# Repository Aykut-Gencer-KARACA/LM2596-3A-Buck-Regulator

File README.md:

<div align="center">

<br/>

<br/><br/>

**Giriş gerilimini düşürüp çıkışa aktaran, trimpotla ayarlanabilir 3 A buck regülatör kartı.**<br/>
LM2596-ADJ ile kurulu bir SMPS (anahtarlamalı güç kaynağı) devresi; üç revizyonda küçültülerek üretime hazır hale getirildi.

</div>

## İçindekiler

- [Genel bakış](#-genel-bakış)
- [Öne çıkanlar](#-öne-çıkanlar)
- [Sistem mimarisi](#-sistem-mimarisi)
- [Çalışma prensibi](#-çalışma-prensibi)
- [Donanım](#-donanım)
- [Tasarım hesapları](#-tasarım-hesapları)
- [Simülasyon](#-simülasyon)
- [Şematik](#-şematik)
- [PCB](#-pcb)
- [Revizyonlar](#-revizyonlar)
- [Malzeme listesi](#-malzeme-listesi)
- [Depo yapısı](#-depo-yapısı)

## ◆ Genel bakış

Bu projede giriş gerilimi düşürülerek çıkışa aktarılır. Giriş gerilimini düşüren bu tip devrelere **SMPS** (Switched-Mode Power Supply) denir; bu projede **LM2596S-ADJ** kullanılmıştır. Çıkış gerilimi, geri besleme bölücüsündeki **RV1** trimpotuyla ayarlanır.

| Özellik | Değer |
|---|---|
| **Regülatör** | LM2596S-ADJ · TO-263-5 · 150 kHz anahtarlama (datasheet) |
| **Çıkış akımı** | 3 A |
| **Giriş gerilimi** | LM2596 için 4.5 – 40 V (datasheet); kondansatörler 50 V |
| **Çıkış gerilimi** | 1.23 V (RV1 = 0) – 13.5 V (RV1 = 10 kΩ), $V_{OUT} = 1.23 \times (1 + R_{V1}/R_1)$ |
| **Bobin** | L1 47 µH · doyma akımı 4.5 A |
| **Serbest dolaşım diyodu** | D1 SS36 · 3 A · 60 V Schottky |
| **Kondansatörler** | C1, C4 470 µF 50 V · C2, C3 100 nF 50 V |
| **Bağlantı** | Giriş ve çıkış için köşelerde 2.2 mm delikli 4 adet pad (IN+, IN−, OUT+, OUT−) · şematikte J1 / J2 olarak çizilen 3.5 mm vida klemens (DB301V-3.5-2P, LCSC C695629) için PCB'de footprint yoktur |
| **Kart (RevC)** | 46.63 × 24.10 mm · 2 katmanlı · 1.6 mm |
| **Maliyet (RevC)** | ≈ 1.05 USD / kart (100 adet) · ≈ 0.83 USD / kart (1000 adet) |

## ◆ Öne çıkanlar

<table>
<tr>
<td width="50%" valign="top">

**Üç revizyonda küçülen kart**<br/>
RevA 56.85 × 32.82 mm, RevB 60.26 × 24.56 mm, RevC 46.63 × 24.10 mm. RevC, RevA'ya göre kart alanını yaklaşık %40 azaltır (1865 mm² → 1124 mm²).

</td>
<td width="50%" valign="top">

**Üretime hazır**<br/>
Güncel sürüm RevC'nin KiCad projesi depoda; LCSC stok kodlu parça listesi ve maliyet tablosu aşağıdaki Malzeme listesi bölümündedir.

</td>
</tr>
<tr>
<td valign="top">

**Ayarlanabilir çıkış**<br/>
Geri besleme direnci 1 kΩ (R1) ile 10 kΩ'luk çok turlu trimpot (RV1) birlikte çıkış gerilimini belirler; ince ayar için 3296W tipi çok turlu trimpot seçildi.

</td>
<td valign="top">

**Seçilmiş pasif parçalar**<br/>
Girişte ve çıkışta 470 µF / 50 V kondansatörler ani akım ihtiyacını karşılar; 100 nF seramikler yüksek frekanslı gürültüyü bastırır.

</td>
</tr>
</table>

## ◆ Sistem mimarisi

Güç yolu soldan sağa akıyor: giriş (J1) önce C1 / C2 filtresinden geçip LM2596'nın `VIN` pinine ulaşıyor. LM2596'nın içindeki anahtar, `OUT` (SW) düğümünü yüksek frekansta giriş gerilimine bağlayıp ayırıyor. Anahtar açıldığında D1, bobin akımını serbest dolaşım yoluyla yüke taşıyor. L1 ve C3 / C4 bir LC süzgeç oluşturup çıkış gerilimini düzeltiyor. Çıkış gerilimi R1 ve RV1 ile bölünüp `FB` pinine geri besleniyor; LM2596 bu pini 1.23 V'ta tutacak şekilde duty'yi ayarlıyor.

## ◆ Çalışma prensibi

Anahtar iletimdeyken (**ON**) akım `V_IN → S → L1 → yük` yolunu izler ve bobin akımı artar. Anahtar açıldığında (**OFF**) bobin akımını sürdürmek ister; D1 iletime geçer ve akım `D1 → L1 → yük` yolunda dolaşarak azalır. Duty oranı çıkış gerilimini belirler:

$$V_{OUT} = D \times V_{IN}$$

## ◆ Donanım

<details open>
<summary><b>Güç katı</b></summary>
<br/>

| Blok | Parça | Not |
|---|---|---|
| Regülatör | U1 LM2596S-ADJ | TO-263-5, 3 A, iç anahtar |
| Bobin | L1 SMMS1040-470M · 47 µH | ISAT 4.5 A · Irms 3 A · DCR 155 mΩ · SMD 11.5 × 10.0 mm (LCSC C149599) |
| Diyot | D1 SS36 · 3 A · 60 V Schottky | DO-214AC (SMA) |
| Giriş kondansatörleri | C1 470 µF 50 V (THT) · C2 100 nF 50 V (0402) | Çıkıştaki ani akım ihtiyacını karşılar ve gerilim çakılmasını önler |
| Çıkış kondansatörleri | C4 470 µF 50 V (THT) · C3 100 nF 50 V (0402) | Çıkıştaki dalgalanmayı (ripple) düşürür |
| Bağlantılar | IN+, IN−, OUT+, OUT− pad'leri | 2.2 mm delikli (3.8 mm pad) lehim noktaları; şematikteki J1 / J2 klemensi PCB'ye yerleştirilmemiştir |

</details>

<details>
<summary><b>Geri besleme</b></summary>
<br/>

- **R1** (1 kΩ, 0805) FB pininden GND'ye bağlıdır.
- **RV1** (10 kΩ, 3296W) çıkış ile FB pini arasında reosta olarak bağlıdır (3 numaralı uç çıkışta, kayar kontak FB'de; 1 numaralı uç boştadır).
- `ON/OFF` pini GND'ye bağlıdır; regülatör her zaman açıktır.

</details>

## ◆ Tasarım hesapları

> Değerler KiCad şematik / PCB dosyalarından (RevC) ve TI LM2596 datasheet'inden (SNVS124G) alınmıştır; her kural için datasheet bölümü belirtilmiştir. Datasheet'te karşılığı olmayan değerler "varsayım" diye işaretlenmiştir.

<details>
<summary><b>Çıkış gerilimi ve geri besleme</b></summary>
<br/>

LM2596 FB pinini $V_{REF} = 1.23\text{ V}$'ta tutar (datasheet 7.8: 1.193 – 1.267 V). R1 FB–GND, RV1 OUT–FB arasında olduğu için (Denklem 5):

$$V_{OUT} = V_{REF} \times \left(1 + \frac{R_{V1}}{R_1}\right) = 1.23\text{ V} \times \left(1 + \frac{R_{V1}}{1\text{ k}\Omega}\right)$$

R1 = 1 kΩ, datasheet'in önerdiği 240 Ω – 1.5 kΩ aralığındadır (9.2.2.2.1). Bölücüden $I_{FB} = 1.23\text{ V} / 1\text{ k}\Omega = 1.23\text{ mA}$ akar; bu, FB bias akımının (tipik 10 nA) yaklaşık $10^5$ katıdır.

| RV1 | V<sub>OUT</sub> | V<sub>FB</sub> toleransıyla |
|---|---|---|
| 0 Ω | 1.23 V | 1.19 – 1.27 V |
| 1 kΩ | 2.46 V | 2.39 – 2.53 V |
| 2 kΩ | 3.69 V | 3.58 – 3.80 V |
| 4 kΩ | 6.15 V | 5.97 – 6.34 V |
| 7 kΩ | 9.84 V | 9.54 – 10.14 V |
| 10 kΩ | 13.53 V | 13.12 – 13.94 V |

3.3 V için $R_{V1} = 1.68\text{ k}\Omega$, 5 V için 3.07 kΩ, 12 V için 8.76 kΩ gerekir. İç anahtarın doyma gerilimi 3 A'de tipik 1.16 V, en fazla 1.4 V (sıcakta 1.5 V); L1'in DCR değeri 155 mΩ (LCSC C149599) olduğundan bobin üzerinde 3 A'de $3 \times 0.155 = 0.47\text{ V}$ düşer. Giriş gerilimi bu yüzden çıkıştan en az $1.16 + 0.47 = 1.63\text{ V}$ (tipik) – $1.4 + 0.47 = 1.87\text{ V}$ (en kötü) yüksek olmalıdır. 10 V'un üzerindeki çıkışlar için datasheet, RV1'e paralel $C_{FF} = 1/(31 \cdot 10^3 \cdot R_2)$ önerir (12 V'ta ≈ 3.7 nF; Tablo 9-6: 1 nF); kartta bu kondansatör yoktur.

RV1'in 1 numaralı ucu boştadır; kayar kontak geçici olarak açık devre olursa FB pinine çıkıştan akım gelmez ve R1 yüzünden FB 0 V'a iner, regülatör duty'yi artırarak çıkışı giriş gerilimine doğru yükseltir. Datasheet'te bu durum anılmaz; trimpotlarda yaygın uygulama, kullanılmayan ucun kayar kontağa bağlanmasıdır.

</details>

<details>
<summary><b>Çalışma noktaları: duty, bobin dalgalanması, tepe akım</b></summary>
<br/>

Datasheet'in duty ifadesi (Denklem 8; $V_{SAT} = 1.16\text{ V}$, $V_D = 0.5\text{ V}$) ve 150 kHz, $L = 47\ \mu\text{H}$ için dalgalanma:

$$D = \frac{V_{OUT} + V_D}{V_{IN} - V_{SAT} + V_D}, \qquad \Delta I_L = \frac{(V_{IN} - V_{SAT} - V_{OUT})\,D}{f_{sw}\,L}, \qquad I_{pk} = I_{LOAD} + \frac{\Delta I_L}{2}$$

| V<sub>IN</sub> → V<sub>OUT</sub> | D | ΔI<sub>L</sub> (pp) | E·T (V·µs) | I<sub>pk</sub> (3 A) | CCM sınırı ΔI<sub>L</sub>/2 |
|---|---|---|---|---|---|
| 12 V → 3.3 V | 0.335 | 0.36 A | 16.8 | 3.18 A | 0.18 A |
| 12 V → 5 V | 0.485 | 0.40 A | 18.9 | 3.20 A | 0.20 A |
| 24 V → 5 V | 0.236 | 0.60 A | 28.0 | 3.30 A | 0.30 A |
| 24 V → 12 V | 0.536 | 0.82 A | 38.7 | 3.41 A | 0.41 A |
| 36 V → 12 V | 0.354 | 1.15 A | 53.9 | 3.57 A | 0.57 A |
| 40 V → 12 V | 0.318 | 1.21 A | 56.9 | 3.60 A | 0.60 A |

Örnek (24 V → 12 V): $D = 12.5 / 23.34 = 0.536$, $\Delta I_L = 10.84 \times 0.536 / (150\text{ kHz} \times 47\ \mu\text{H}) = 0.82\text{ A}$.

</details>

<details>
<summary><b>Bobin kontrolü</b></summary>
<br/>

Datasheet'in örnek tasarımı (9.2.2.2.2, 28 V → 20 V, 3 A) $E \cdot T = 34.2\text{ V}\cdot\mu\text{s}$ bulup 47 µH seçer; kartın 24 V → 12 V noktası 38.7 V·µs olduğundan 47 µH aynı bölgededir. 12 – 24 V girişte tepe akım ≤ 3.41 A, yani ISAT'ın (4.5 A) %76'sıdır. 40 V → 12 V, 3 A noktasında tepe akım 3.60 A olur ve LM2596'nın en küçük akım sınırına (3.6 A, datasheet 7.9) eşittir; bu bölgede 68 µH bobin tercih edilmelidir.

LCSC kaydına göre L1 (SMMS1040-470M): 47 µH ±%20, Irms 3 A, ISAT 4.5 A, DCR 155 mΩ. 3 A'de bakır kaybı $P_L = I^2 \times DCR = 3^2 \times 0.155 = 1.40\text{ W}$'tır ve nominal akım (3 A) ile yük akımı eşittir; yani bobin tam yükte kendi sıcaklık artış sınırında çalışır.

</details>

<details>
<summary><b>Serbest dolaşım diyodu (D1)</b></summary>
<br/>

| Kural (datasheet 9.2.2.2.5) | Gerekli | SS36 | Sonuç |
|---|---|---|---|
| Ters gerilim ≥ 1.25 × V<sub>IN,max</sub> | 1.25 × 40 V = 50 V | 60 V | sağlanıyor |
| Akım ≥ 1.3 × I<sub>LOAD</sub> | 1.3 × 3 A = 3.9 A | 3 A | sağlanmıyor |
| Sürekli kısa devre: akım ≥ I<sub>CL</sub> | 4.5 A (tipik) | 3 A | sağlanmıyor |

Normal çalışmada ortalama diyot akımı $I_D = I_{LOAD}(1 - D)$ ve kaybı $P_D = 0.5\text{ V} \times I_D$: 12 V → 5 V için 1.54 A / 0.77 W, 24 V → 12 V için 1.39 A / 0.70 W, 24 V → 5 V için 2.29 A / 1.15 W. Normal yükte 3 A'lik diyot yeterlidir; kalıcı kısa devre dayanımı için 5 A sınıfı gerekir.

</details>

<details>
<summary><b>Kondansatörler</b></summary>
<br/>

- **C1 (giriş):** RMS akım değeri $\ge I_{LOAD}/2 = 1.5\text{ A}$ ve gerilim değeri $\approx 1.5 \times V_{IN}$ olmalıdır (9.2.2.2.6); 50 V için bu $V_{IN} \le 33\text{ V}$ demektir. RMS değeri üretici datasheet'inden doğrulanmalıdır (şematikte parça numarası yoktur, BOM'daki 01EC4236 kodu doğrulanamadı).
- **C4 (çıkış):** datasheet 82 – 820 µF aralığını ve $\ge 1.5 \times V_{OUT}$ gerilim değerini ister (9.2.2.2.3); 470 µF / 50 V bunu sağlar (13.5 V için gereken 20.3 V).
- **Çıkış dalgalanması:** $V_{rip} = \Delta I_L \cdot ESR$; 24 V → 12 V noktasında kapasitif bileşen $\Delta I_L / (8 f_{sw} C) = 1.5\text{ mV}$ (ihmal edilebilir). ESR bileşeni (ESR varsayım): 0.05 Ω için 41 mV, 0.1 Ω için 82 mV, 0.2 Ω için 165 mV (pp).

$$f_0 = \frac{1}{2\pi\sqrt{L_1 C_4}} = \frac{1}{2\pi\sqrt{47\ \mu\text{H} \times 470\ \mu\text{F}}} \approx 1.07\text{ kHz} \quad\Rightarrow\quad \frac{150\text{ kHz}}{1.07\text{ kHz}} \approx 140$$

</details>

<details>
<summary><b>Güç kaybı ve ısıl kontrol</b></summary>
<br/>

İç anahtarın iletim ve besleme kaybı (alt sınır): $P_{IC,min} = V_{SAT}\,I_{LOAD}\,D + V_{IN}\,I_Q$ ($I_Q = 5\text{ mA}$). Üst sınır, datasheet'in tipik verimlerinden (12 V → 5 V için %80, 25 V → 12 V için %90, 3 A) toplam kayıptan diyot kaybının düşülmesiyle bulunur:

| V<sub>IN</sub> → V<sub>OUT</sub>, 3 A | P<sub>OUT</sub> | η | P<sub>kayıp</sub> | P<sub>D1</sub> | P<sub>L1</sub> (1.40 W) çıkarılınca P<sub>IC</sub> | İletim modeli P<sub>IC</sub> |
|---|---|---|---|---|---|---|
| 12 V → 5 V | 15 W | %80 | 3.75 W | 0.77 W | 1.58 W | 1.75 W |
| 24 V → 12 V | 36 W | %90 | 4.00 W | 0.70 W | 1.90 W | 1.98 W |

İki yöntem birbirine yakındır (1.6 – 2.0 W); yani entegrenin gücü yaklaşık 2 W kabul edilebilir. TO-263 için R<sub>θJA</sub> bakır alanına bağlıdır (datasheet 7.4): 0.5 in² → 50 °C/W, 2.5 in² → 30 °C/W, çift yüzlü 3 in² → 20 °C/W. Kartın tüm alanı $46.63 \times 24.10 = 1124\text{ mm}^2 \approx 1.74\text{ in}^2$ olduğundan 30 – 50 °C/W beklenir. 125 °C sınırı ve 40 °C ortam için izin verilen güç ve 24 V → 12 V, 3 A noktasındaki sıcaklık:

$$P_{IC,max} = \frac{125 - 40}{R_{\theta JA}} = 1.70\text{ W}\ (50\ ^\circ\text{C/W}),\quad 2.83\text{ W}\ (30\ ^\circ\text{C/W}) \qquad T_J = 40 + 1.98 \times R_{\theta JA} = 99\ ^\circ\text{C}\ (30),\quad 139\ ^\circ\text{C}\ (50)$$

R<sub>θJA</sub> = 30 °C/W kadar bakır sağlanıyorsa 3 A tam yük sınırın içindedir; 50 °C/W'ta (az bakır) 125 °C aşılır. Sürekli yük yaklaşık 2 A tutulursa entegre gücü yaklaşık 1.4 W'a (T<sub>J</sub> ≤ 110 °C) düşer. Datasheet 2 A üstünde çift yüzlü kart, geniş bakır alan veya hava akışı önerir (9.4.3); bu nedenle gerçek sıcaklık ölçülmelidir. 24 V → 12 V, 3 A noktasında giriş akımı $36 / (0.9 \times 24) = 1.67\text{ A}$'dir.

</details>

<details>
<summary><b>Seçim gerekçeleri</b></summary>
<br/>

- **Bobin:** RevA'da 68 µH kullanıldı; RevB / RevC'de stok durumu ve maliyet nedeniyle 47 µH (SMMS1040) kullanıldı.
- **Diyot:** Devreden geçecek akım 3 A düzeyinde olacağından serbest dolaşım diyodu Schottky olarak seçildi. RevA'da 5 A'lik bir diyot düşünülmüştü, RevB / RevC'de maliyet için 3 A / 60 V SS36'ya geçildi.
- **Kondansatörler:** Girişte ve çıkışta 50 V dayanımlı 470 µF polarize kondansatörler kullanıldı; RevA'da çıkışta 35 V'luk 220 µF kondansatörler vardı.

</details>

## ◆ Simülasyon

LTspice simülasyon sonucu (Temmuz 2026, tasarımın ilk aşamasında alınmıştır):

## ◆ Şematik

## ◆ PCB

<table>
<tr>
<td width="50%"></td>
<td width="50%"></td>
</tr>
<tr>
<td align="center"><sub>Hero görünüm (sol önden, 3/4) · RevC</sub></td>
<td align="center"><sub>Üstten görünüm · 46.63 × 24.10 mm</sub></td>
</tr>
</table>

Görseller [DRC Analyzer](https://github.com/Aykut-Gencer-KARACA/DRC-Analyzer) ile projenin 3B modelinden üretilmiştir; tam çözünürlüklü dosyalar `KiCad Project/Renders/` klasöründedir.

## ◆ Revizyonlar

**Güncel sürüm: RevC.** Revizyonlar arasında bileşenler stok durumu ve üretim maliyeti nedeniyle değişmiştir.

| | RevA | RevB | RevC |
|---|---|---|---|
| **Kart boyutu** | 56.85 × 32.82 mm | 60.26 × 24.56 mm | 46.63 × 24.10 mm |
| **Bobin (L1)** | 68 µH | 47 µH (SMMS1040) | 47 µH (SMMS1040) |
| **Giriş kondansatörleri** | 2 × 470 µF 50 V | 470 µF 50 V + 100 nF | 470 µF 50 V + 100 nF |
| **Çıkış kondansatörleri** | 2 × 220 µF 35 V | 470 µF 50 V + 100 nF | 470 µF 50 V + 100 nF |
| **Diyot (D1)** | Schottky (genel) | SS36 (3 A, 60 V) | SS36 (3 A, 60 V) |

RevB ve RevC aynı parça listesini kullanır; RevC bu parçaları daha küçük bir kartta toplar.

> [!NOTE]
> RevA'da LM2596 çıkışına paralel bağlı 220 µF kondansatörler ve 5 A'lik Schottky diyot kullanılmıştı. Depoda yalnızca güncel sürüm RevC'nin dosyaları bulunur.

## ◆ Malzeme listesi

<details>
<summary><b>RevC · parça listesi ve maliyet</b> (LCSC stok kodları ve fiyatları)</summary>
<br/>

| Ref | Açıklama | Parça | Adet | Kılıf | Stok kodu |
|---|---|---|:-:|---|---|
| U1 | Buck regülatör | LM2596S-ADJ | 1 | TO-263-5L | LM2596S-ADJ |
| L1 | Güç bobini 47 µH, ISAT 4.5 A, DCR 155 mΩ | SMMS1040-470M | 1 | SMD 11.5 × 10.0 | C149599 |
| D1 | Schottky diyot 3 A / 60 V | SS36 | 1 | DO-214AC | SS36 |
| C1, C4 | 470 µF 50 V | 01EC4236 (doğrulanamadı); footprint'e uyan örnek: Lelon RGA471M1HBK-1020G | 2 | THT D10 × L20, P = 5 mm | 01EC4236 (örnek: C134595) |
| C2, C3 | 100 nF 50 V | C0402B104K500NT | 2 | 0402 | C0402B104K500NT |
| R1 | 1 kΩ, 125 mW | FRC0805F1001TS | 1 | 0805 | FRC0805F1001TS |
| RV1 | 10 kΩ çok turlu trimpot | 3296W-103-LF | 1 | THT 9.5 × 4.8 mm | 3296W-103-LF |
| J1, J2 | Vida klemens, 2 kutuplu, 3.5 mm (7 A, 300 V) · şematikte tanımlı, PCB'de footprint yok | DB301V-3.5-2P-GN-S | 2 | THT | C695629 |

**Maliyet** (parçalar LCSC fiyatlarıyla, kart başına):

| Adet | Toplam | Kart başına | Klemenssiz kart başına |
|---|---|---|---|
| 100 | 104.88 USD | 1.05 USD | 0.93 USD |
| 500 | 438.00 USD | 0.88 USD | 0.78 USD |
| 1000 | 827.90 USD | 0.83 USD | 0.73 USD |

Maliyetler LCSC birim fiyatlarından hesaplanmıştır; fiyatlar ve stok adetleri değişebilir.

</details>

## ◆ Depo yapısı

```text
LM2596-3A-Buck-Regulator/
├─ KiCad Project/                          KiCad projesi (güncel sürüm: RevC)
│  ├─ LM2596-Buck-Regulator.kicad_pro / _sch / _pcb
│  ├─ Layer_Images/                         Katman görüntüleri, şematik PDF, 3D .glb
│  ├─ Renders/                              Yüksek çözünürlüklü PCB render'ı
│  ├─ EasyEDA.kicad_sym                     Sembol kütüphanesi
│  ├─ EasyEDA.pretty/                       Footprint'ler
│  └─ EasyEDA.3dshapes/                     3D modeller
├─ assets/                                 README görselleri
└─ README.md
```

Projeyi açmak için KiCad'de `KiCad Project/LM2596-Buck-Regulator.kicad_pro` dosyasını açın. Revizyon bilgisi şemanın ve PCB'nin başlık bloğundadır.

<br/>

<div align="center">

<br/>
<sub>LM2596 · 47 µH · SS36 · KiCad</sub>
</div>

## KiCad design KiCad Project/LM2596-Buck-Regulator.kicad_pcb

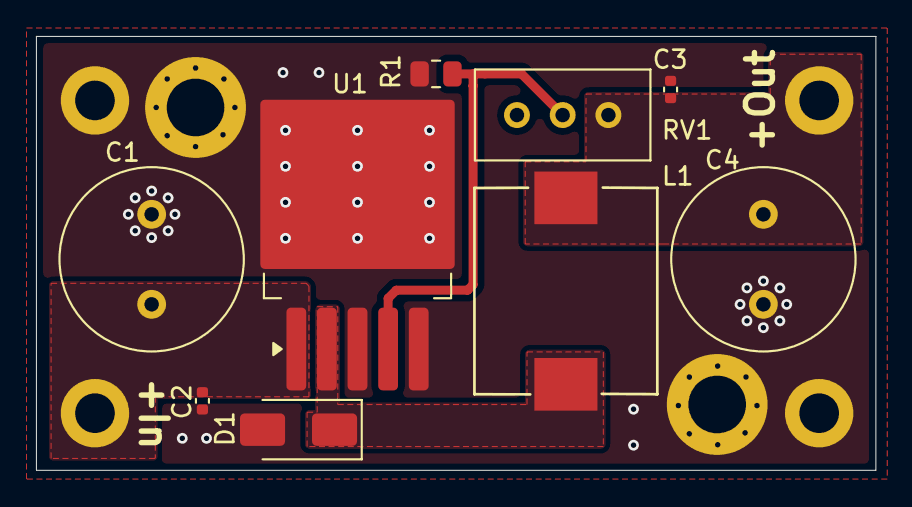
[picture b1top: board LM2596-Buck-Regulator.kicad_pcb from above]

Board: 2 copper layers, 46.6 x 24.1 mm, 9 parts (0 on the bottom side), 5 nets.

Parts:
C1, C4: 470 uF 50 V; C_Radial_D10.0mm_H20.0mm_P5.00mm
C2, C3: 100 nF 50 V; C_0402_1005Metric
D1: 3A 60 V; D_SMA
L1: 47 uH 3A ISAT 4.5 A; IND-SMD_L11.5-W10.0_SMMS1040
R1: 1K Ohm 150 V 125 mW; R_0805_2012Metric
RV1: 10 K Ohm Multiturn; Potentiometer_Bourns_3296W_Vertical
U1: LM2596S-ADJ; TO-263-5_TabPin3

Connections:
GND: C1.2, C2.2, C3.2, C4.2, D1.2 (A), R1.1, U1.3 (GND), U1.5 (~ON/OFF)
unnamed: D1.1 (K), L1.1, U1.2 (OUT)
unnamed: C1.1, C2.1, U1.1 (VIN)
unnamed: C3.1, C4.1, L1.2, RV1.3
unnamed: R1.2, RV1.2, U1.4 (FB)

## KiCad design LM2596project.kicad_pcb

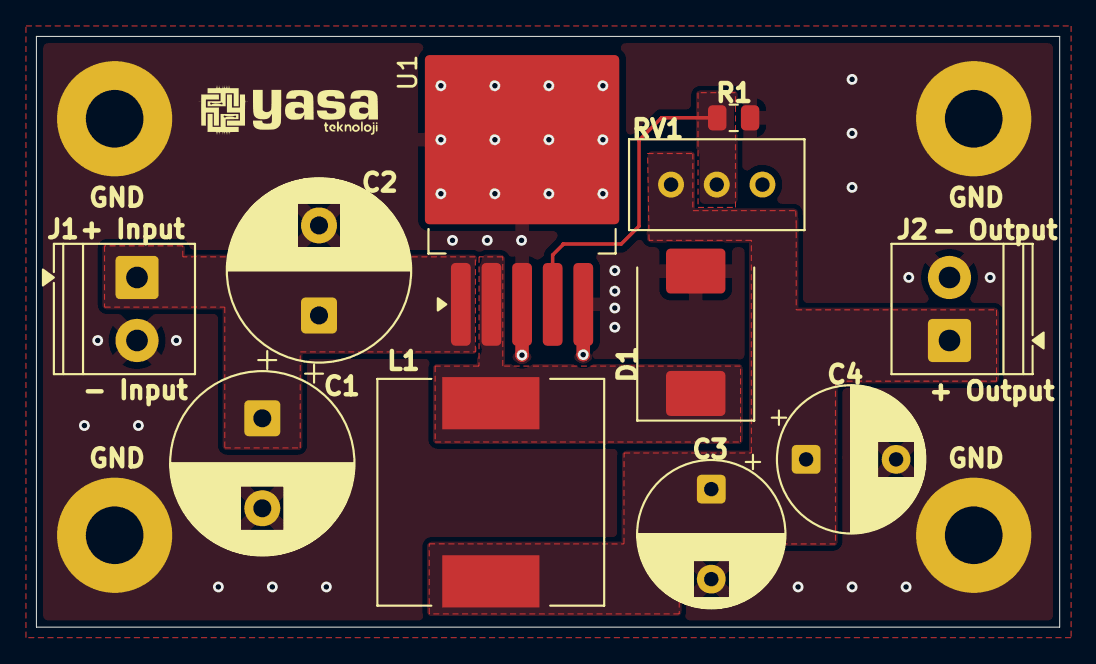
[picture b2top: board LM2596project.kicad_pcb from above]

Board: 2 copper layers, 56.8 x 32.8 mm, 11 parts (0 on the bottom side), 5 nets.

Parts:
C1, C2: 470 uF 50V; CP_Radial_D10.0mm_P5.00mm
C3, C4: 220 uF 35V; CP_Radial_D8.0mm_P5.00mm
D1: D_Schottky; D_SMC
J1, J2: Screw_Terminal_01x02; TerminalBlock_Phoenix_PT-1,5-2-3.5-H_1x02_P3.50mm_Horizontal
L1: 68 uH; L_12x12mm_H8mm
R1: 1 kOhm; R_0805_2012Metric
RV1: 10K Multiturn Clockwise; Potentiometer_Bourns_3296W_Vertical
U1: LM2596S-ADJ; TO-263-5_TabPin3

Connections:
GND: C1.2, C2.2, C3.2, C4.2, D1.2 (A), J1.2, J2.2, R1.1, U1.3 (GND)
unnamed: D1.1 (K), L1.1, U1.2 (OUT)
unnamed: C1.1, C2.1, J1.1, U1.1 (VIN)
unnamed: C3.1, C4.1, J2.1, L1.2, RV1.3
unnamed: R1.2, RV1.2, U1.4 (FB)
